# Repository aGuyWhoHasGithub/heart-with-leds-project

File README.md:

Copyright (c) 2024 Franco Gonzalez Liotta. All rights reserved. Copyright applies to all files uploaded to this repository.

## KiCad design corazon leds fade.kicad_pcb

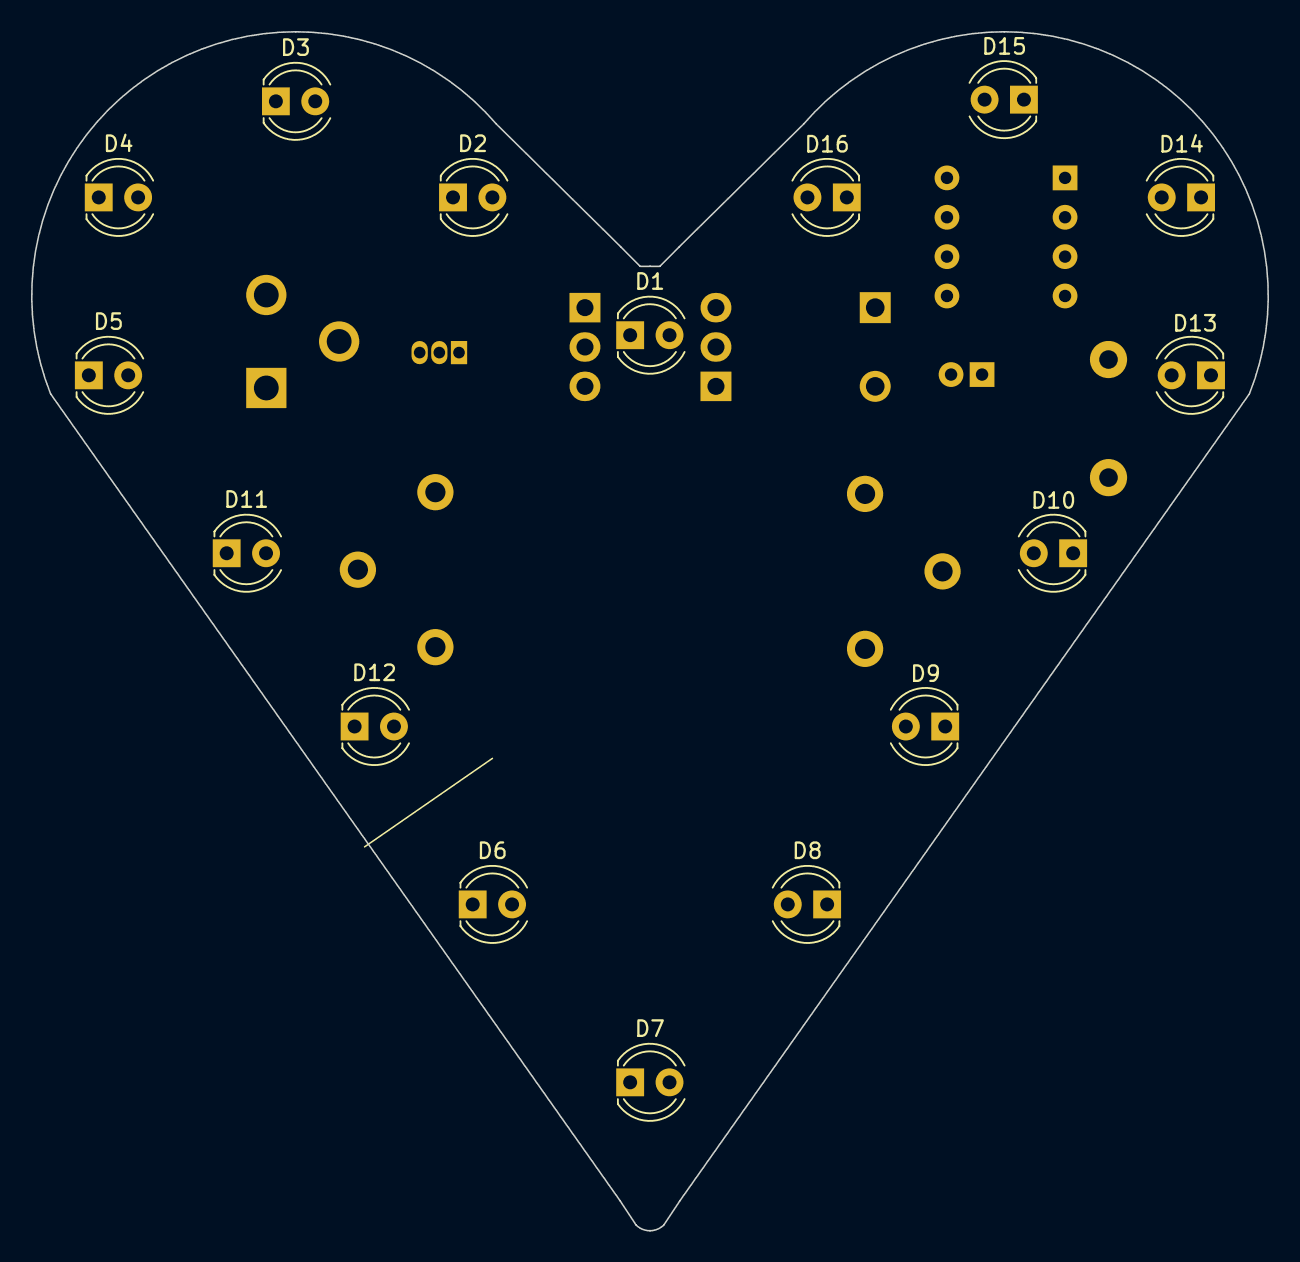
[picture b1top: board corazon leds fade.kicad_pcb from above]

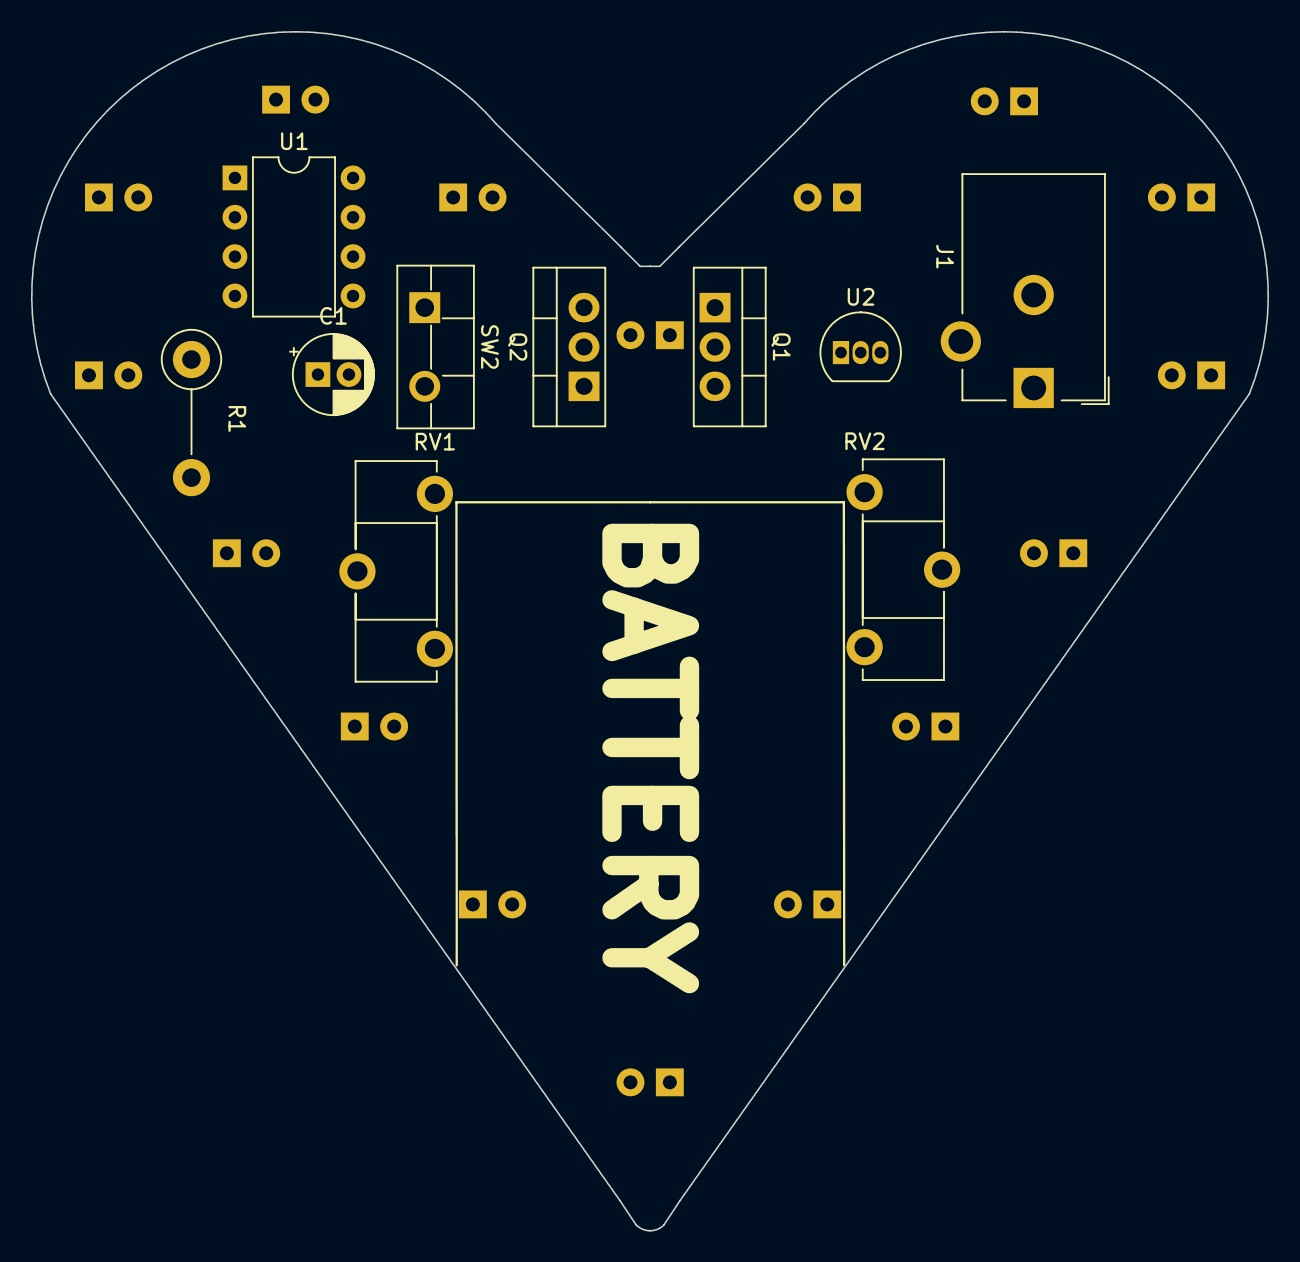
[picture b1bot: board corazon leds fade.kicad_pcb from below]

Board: 2 copper layers, 79.8 x 77.4 mm, 26 parts (10 on the bottom side), 17 nets, no tracks yet.

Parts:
C1: C_Polarized; CP_Radial_D5.0mm_P2.00mm
D1, D2, D3, D4, D5, D6, D7, D8, D9, D10, D11, D12, D13, D14, D15, D16: LED; LED_D4.0mm
J1: Jack-DC; BarrelJack_CUI_PJ-102AH_Horizontal
Q1, Q2: NMOS; TO-220-3_Vertical
R1: R; R_Axial_DIN0411_L9.9mm_D3.6mm_P7.62mm_Vertical
RV1, RV2: R_Potentiometer; Potentiometer_ACP_CA14-H5_Horizontal
SW2: SW_SPST; TO-220F-2_Vertical
U1: NE555P; DIP-8_W7.62mm
U2: L78L05_TO92; TO-92_Inline

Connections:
unnamed: C1.2, RV1.2
unnamed: D1.2 (A), D2.2 (A), D3.2 (A), D4.2 (A), D5.2 (A), D11.2 (A), D12.2 (A), Q1.3 (S)
unnamed: D1.1 (K), D10.1 (K), J1.2, RV1.1, U1.1 (GND), U2.2 (GND)
unnamed: D2.1 (K), D8.1 (K)
unnamed: D3.1 (K), D7.1 (K)
unnamed: D4.1 (K), D6.1 (K)
unnamed: D5.1 (K), D9.1 (K)
unnamed: D6.2 (A), D7.2 (A), D8.2 (A), D9.2 (A), D10.2 (A), D13.2 (A), D14.2 (A), Q2.3 (S)
unnamed: D11.1 (K), D13.1 (K)
unnamed: D12.1 (K), D14.1 (K)
unnamed: Q1.1 (D), Q2.1 (D), RV2.2
unnamed: C1.1, Q1.2 (G), Q2.2 (G), U1.3 (Q)
unnamed: R1.1, SW2.1 (A)
unnamed: SW2.2 (B), U2.1 (VO)
unnamed: R1.2, RV2.1, U1.4 (R), U1.8 (VCC)
unnamed: U1.2 (TR), U1.6 (THR)
unnamed: J1.1, U2.3 (VI)

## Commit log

2024-08-06 corazon leds fade.kicad_pcb
2024-08-06 COPYRIGHT.md
